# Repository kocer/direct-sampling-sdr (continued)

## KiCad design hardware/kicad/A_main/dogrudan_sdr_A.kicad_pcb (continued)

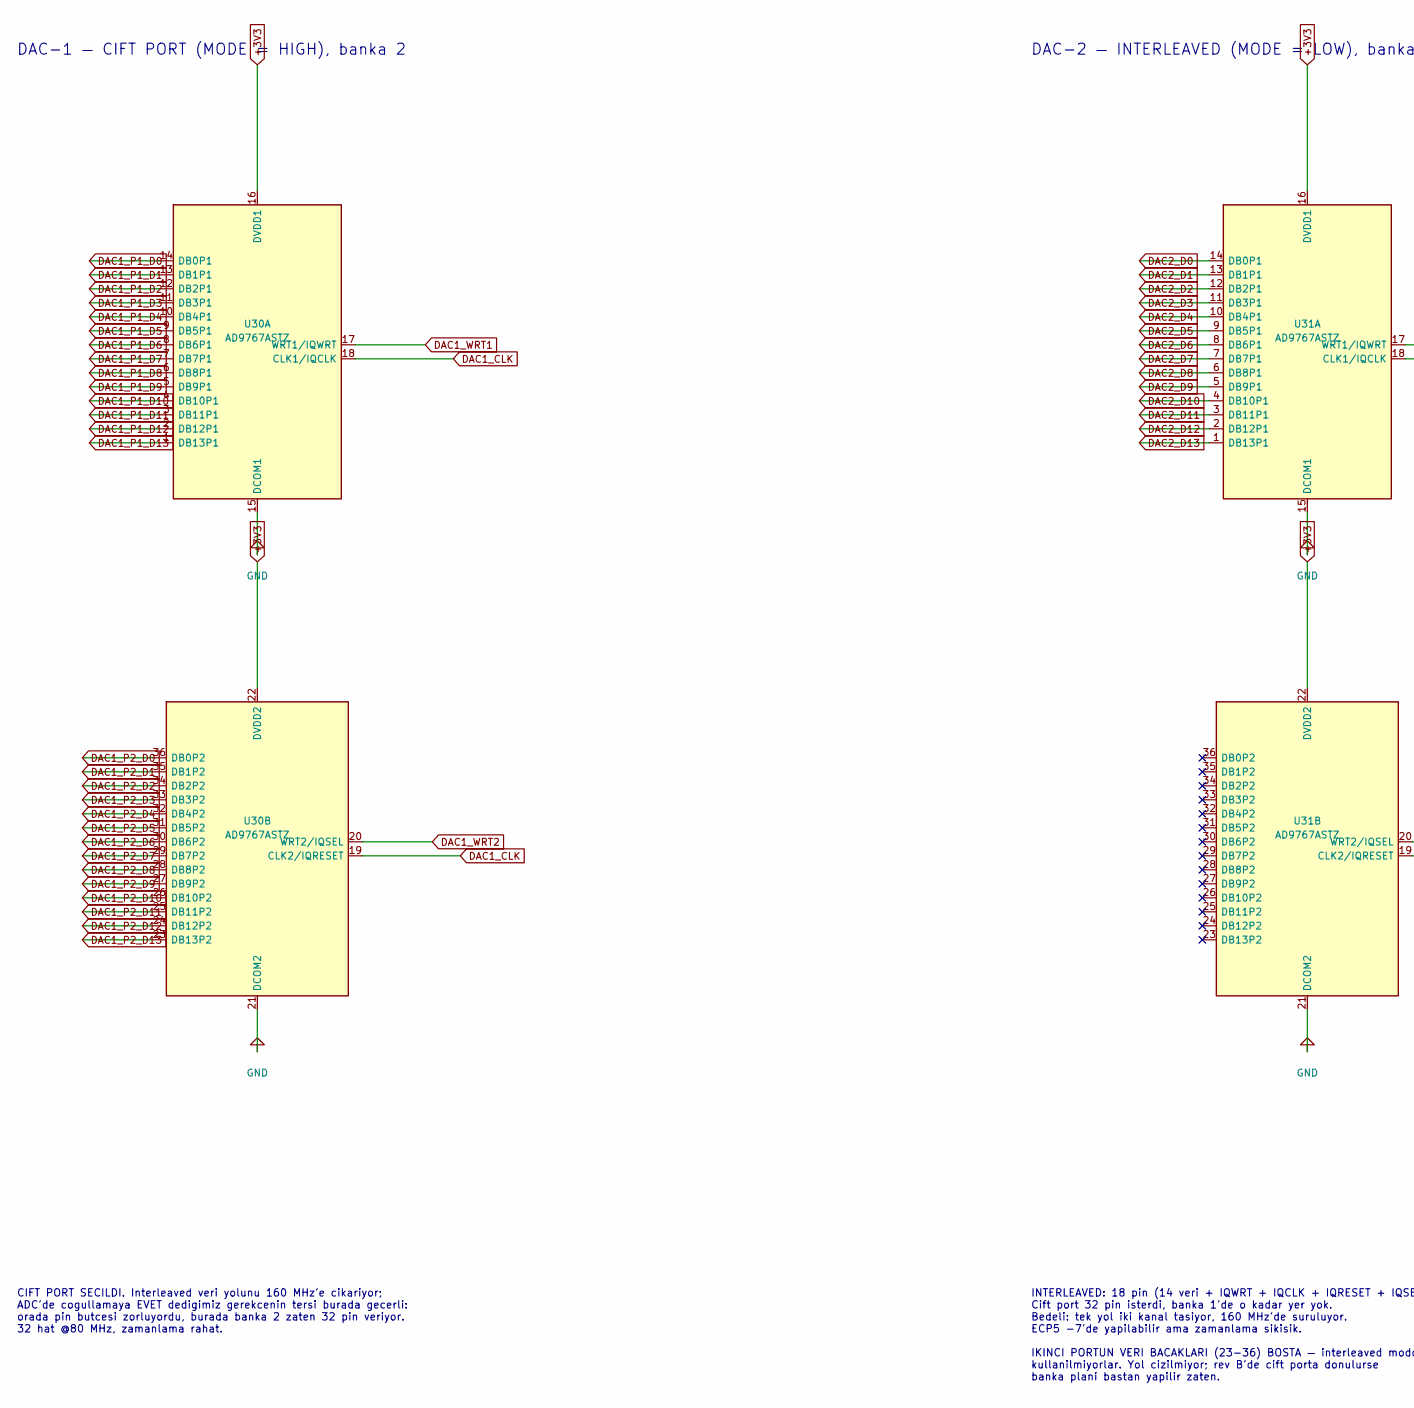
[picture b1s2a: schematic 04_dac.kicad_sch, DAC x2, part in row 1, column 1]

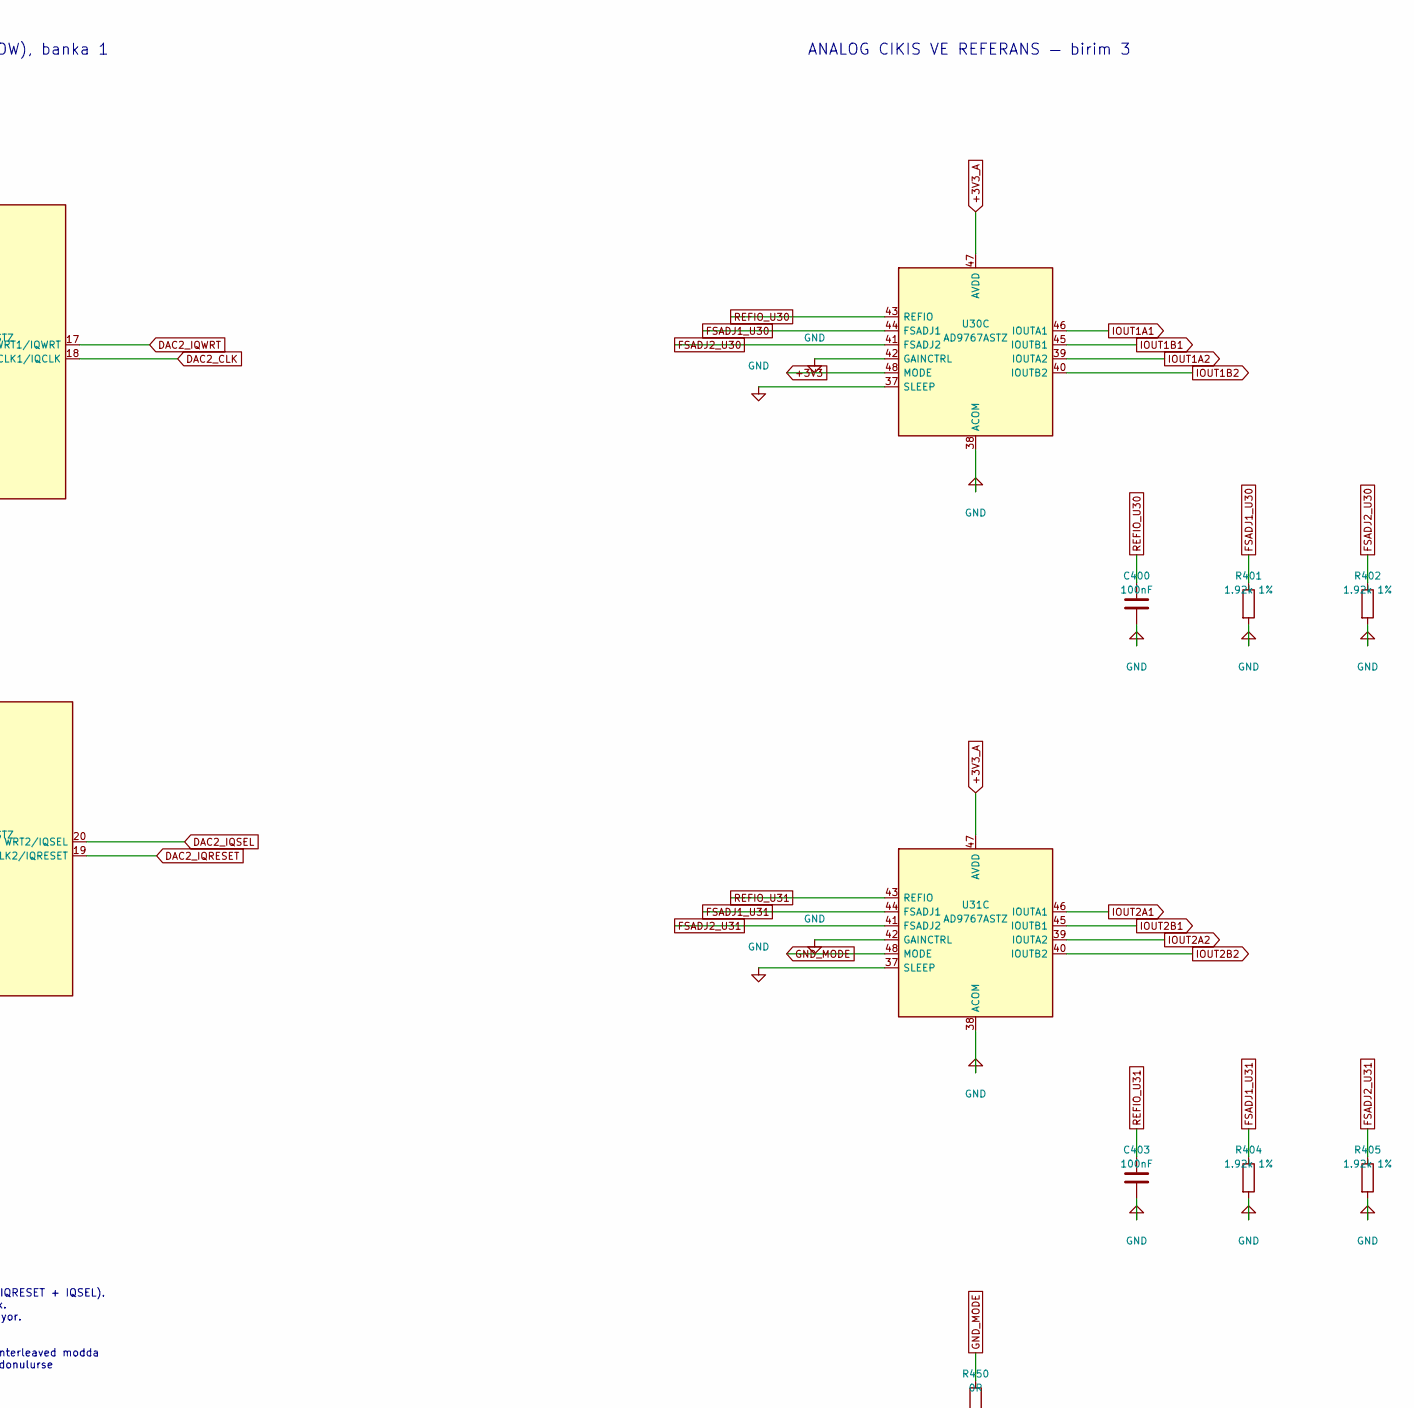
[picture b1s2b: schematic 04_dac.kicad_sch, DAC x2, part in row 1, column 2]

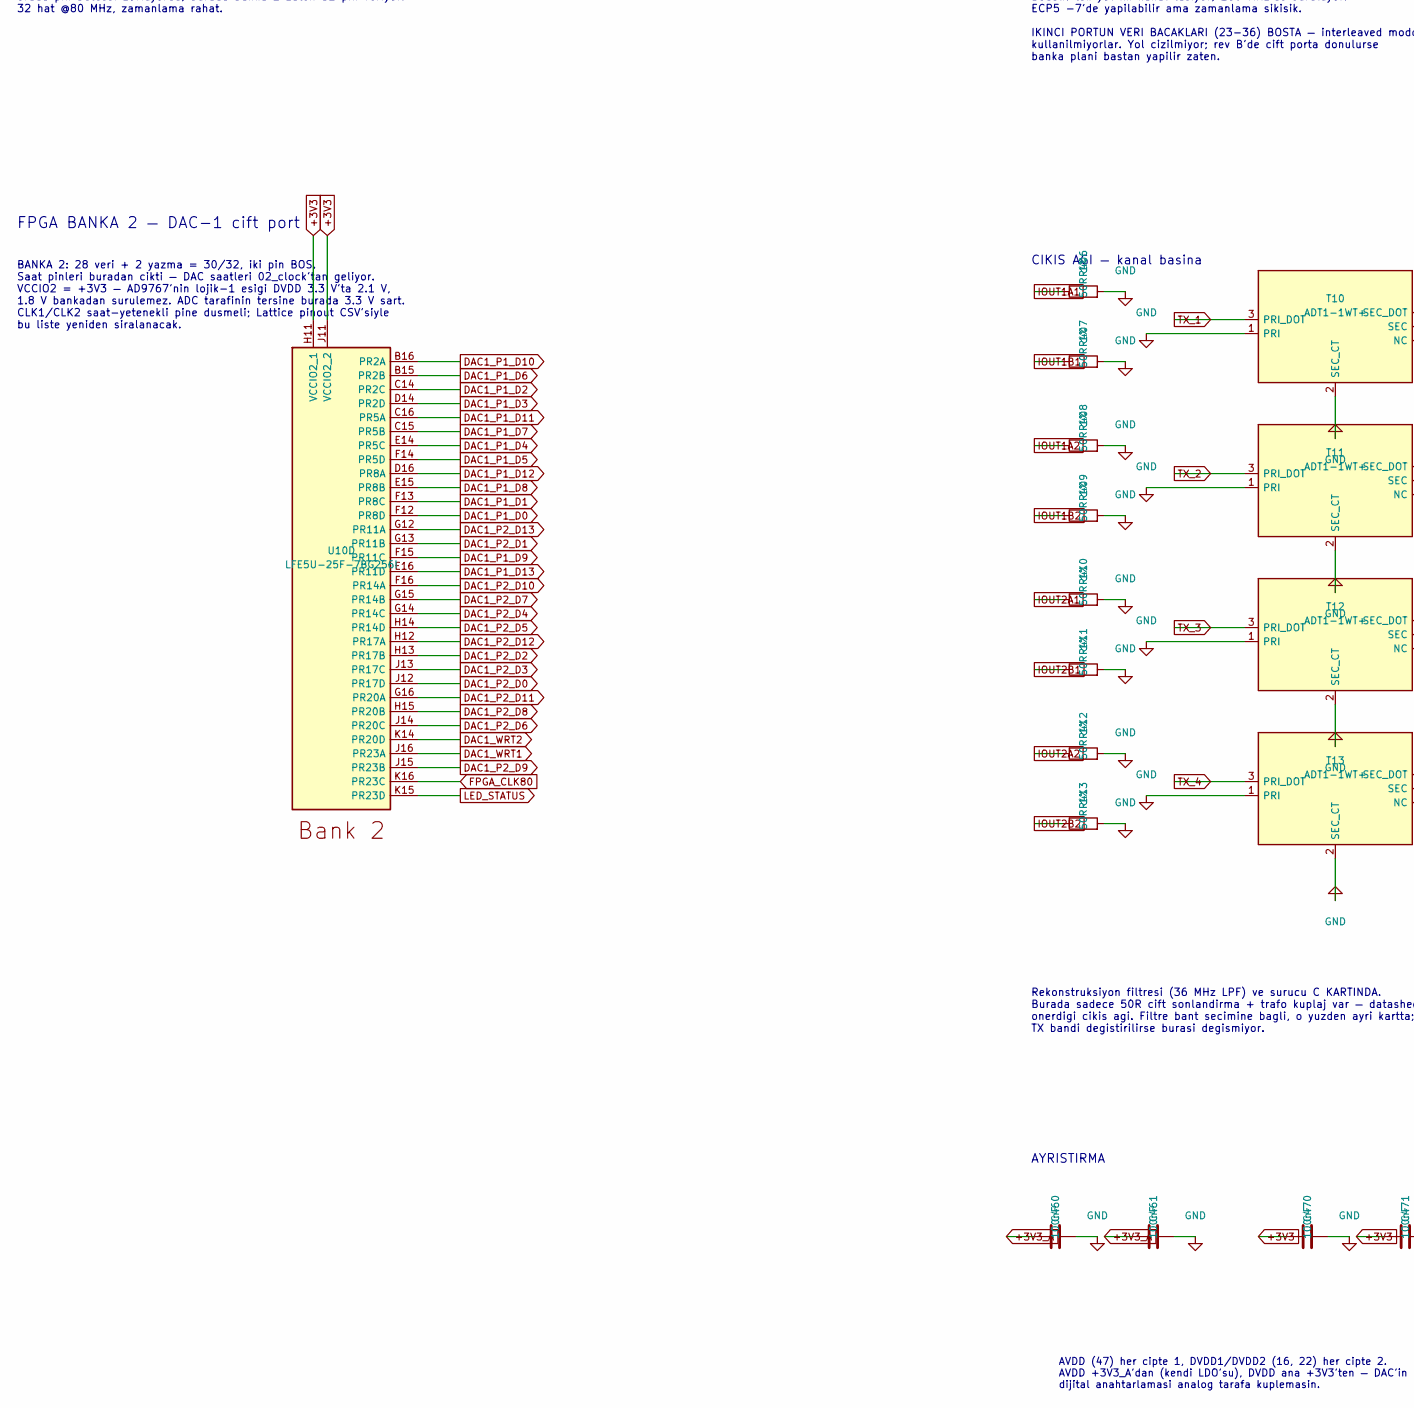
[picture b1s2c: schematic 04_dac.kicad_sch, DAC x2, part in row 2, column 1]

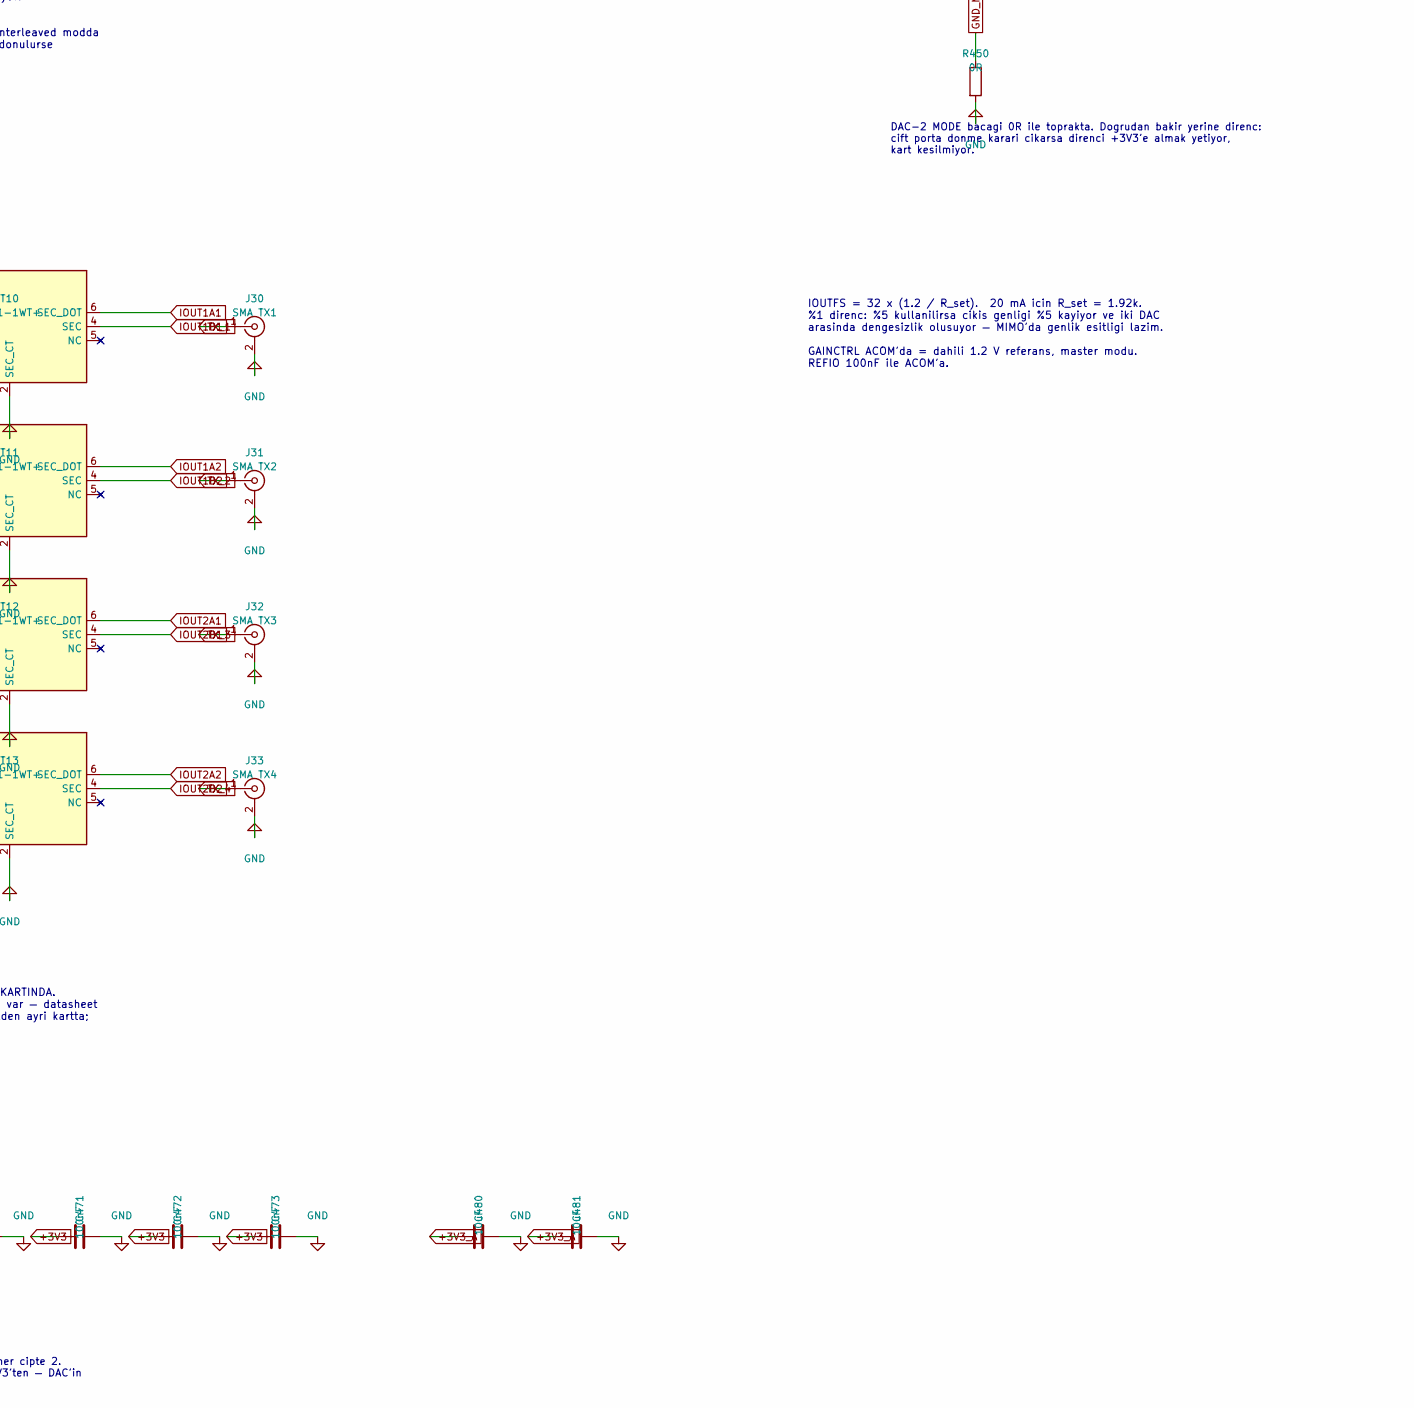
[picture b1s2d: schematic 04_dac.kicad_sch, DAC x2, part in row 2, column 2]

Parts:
C400, C403: 100nF; C_0603_1608Metric
C460, C461, C470, C471, C472, C473: 100nF; C_0402_1005Metric
C480, C481: 10uF; C_0402_1005Metric
J30: SMA TX1; SMA_Amphenol_132289_EdgeMount
J31: SMA TX2; SMA_Amphenol_132289_EdgeMount
J32: SMA TX3; SMA_Amphenol_132289_EdgeMount
J33: SMA TX4; SMA_Amphenol_132289_EdgeMount
R401, R402, R404, R405: 1.92k 1%; R_0603_1608Metric
R406, R407, R408, R409, R410, R411, R412, R413: 50R 1%; R_0603_1608Metric
R450: 0R; R_0603_1608Metric
T10, T11, T12, T13: ADT1-1WT+; Mini-Circuits_CD542_H2.84mm
U10: LFE5U-25F-7BG256I; BGA-256_14.0x14.0mm_Layout16x16_P0.8mm_Ball0.45mm_Pad0.32mm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
U30, U31: AD9767ASTZ; LQFP-48_7x7mm_P0.5mm

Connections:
DAC1_CLK: U30.18 (CLK1/IQCLK), U30.19 (CLK2/IQRESET); also elsewhere on the board
DAC1_P1_D0: U10.F12 (PR8D), U30.14 (DB0P1)
DAC1_P1_D1: U10.F13 (PR8C), U30.13 (DB1P1)
DAC1_P1_D2: U10.C14 (PR2C), U30.12 (DB2P1)
DAC1_P1_D3: U10.D14 (PR2D), U30.11 (DB3P1)
DAC1_P1_D4: U10.E14 (PR5C), U30.10 (DB4P1)
DAC1_P1_D5: U10.F14 (PR5D), U30.9 (DB5P1)
DAC1_P1_D6: U10.B15 (PR2B), U30.8 (DB6P1)
DAC1_P1_D7: U10.C15 (PR5B), U30.7 (DB7P1)
DAC1_P1_D8: U10.E15 (PR8B), U30.6 (DB8P1)
DAC1_P1_D9: U10.F15 (PR11C), U30.5 (DB9P1)
DAC1_P1_D10: U10.B16 (PR2A), U30.4 (DB10P1)
DAC1_P1_D11: U10.C16 (PR5A), U30.3 (DB11P1)
DAC1_P1_D12: U10.D16 (PR8A), U30.2 (DB12P1)
DAC1_P1_D13: U10.E16 (PR11D), U30.1 (DB13P1)
DAC1_P2_D0: U10.J12 (PR17D), U30.36 (DB0P2)
DAC1_P2_D1: U10.G13 (PR11B), U30.35 (DB1P2)
DAC1_P2_D2: U10.H13 (PR17B), U30.34 (DB2P2)
DAC1_P2_D3: U10.J13 (PR17C), U30.33 (DB3P2)
DAC1_P2_D4: U10.G14 (PR14C), U30.32 (DB4P2)
DAC1_P2_D5: U10.H14 (PR14D), U30.31 (DB5P2)
DAC1_P2_D6: U10.J14 (PR20C), U30.30 (DB6P2)
DAC1_P2_D7: U10.G15 (PR14B), U30.29 (DB7P2)
DAC1_P2_D8: U10.H15 (PR20B), U30.28 (DB8P2)
DAC1_P2_D9: U10.J15 (PR23B), U30.27 (DB9P2)
DAC1_P2_D10: U10.F16 (PR14A), U30.26 (DB10P2)
DAC1_P2_D11: U10.G16 (PR20A), U30.25 (DB11P2)
DAC1_P2_D12: U10.H12 (PR17A), U30.24 (DB12P2)
DAC1_P2_D13: U10.G12 (PR11A), U30.23 (DB13P2)
DAC1_WRT1: U10.J16 (PR23A), U30.17 (WRT1/IQWRT)
DAC1_WRT2: U10.K14 (PR20D), U30.20 (WRT2/IQSEL)
DAC2_CLK: U31.18 (CLK1/IQCLK); also elsewhere on the board
DAC2_D0: U31.14 (DB0P1); also elsewhere on the board
DAC2_D1: U31.13 (DB1P1); also elsewhere on the board
DAC2_D2: U31.12 (DB2P1); also elsewhere on the board
DAC2_D3: U31.11 (DB3P1); also elsewhere on the board
DAC2_D4: U31.10 (DB4P1); also elsewhere on the board
DAC2_D5: U31.9 (DB5P1); also elsewhere on the board
DAC2_D6: U31.8 (DB6P1); also elsewhere on the board
DAC2_D7: U31.7 (DB7P1); also elsewhere on the board
DAC2_D8: U31.6 (DB8P1); also elsewhere on the board
DAC2_D9: U31.5 (DB9P1); also elsewhere on the board
DAC2_D10: U31.4 (DB10P1); also elsewhere on the board
DAC2_D11: U31.3 (DB11P1); also elsewhere on the board
DAC2_D12: U31.2 (DB12P1); also elsewhere on the board
DAC2_D13: U31.1 (DB13P1); also elsewhere on the board
DAC2_IQRESET: U31.19 (CLK2/IQRESET); also elsewhere on the board
DAC2_IQSEL: U31.20 (WRT2/IQSEL); also elsewhere on the board
DAC2_IQWRT: U31.17 (WRT1/IQWRT); also elsewhere on the board
FPGA_CLK80: U10.K16 (PR23C); also elsewhere on the board
FSADJ1_U30: R401.1, U30.44 (FSADJ1)
FSADJ1_U31: R404.1, U31.44 (FSADJ1)
FSADJ2_U30: R402.1, U30.41 (FSADJ2)
FSADJ2_U31: R405.1, U31.41 (FSADJ2)
GND_MODE: R450.1, U31.48 (MODE)
IOUT1A1: R406.1, T10.6 (SEC_DOT), U30.46 (IOUTA1)
IOUT1A2: R408.1, T11.6 (SEC_DOT), U30.39 (IOUTA2)
IOUT1B1: R407.1, T10.4 (SEC), U30.45 (IOUTB1)
IOUT1B2: R409.1, T11.4 (SEC), U30.40 (IOUTB2)
IOUT2A1: R410.1, T12.6 (SEC_DOT), U31.46 (IOUTA1)
IOUT2A2: R412.1, T13.6 (SEC_DOT), U31.39 (IOUTA2)
IOUT2B1: R411.1, T12.4 (SEC), U31.45 (IOUTB1)
IOUT2B2: R413.1, T13.4 (SEC), U31.40 (IOUTB2)
LED_STATUS: U10.K15 (PR23D); also elsewhere on the board
TX_1: J30.1 (In), T10.3 (PRI_DOT)
TX_2: J31.1 (In), T11.3 (PRI_DOT)
TX_3: J32.1 (In), T12.3 (PRI_DOT)
TX_4: J33.1 (In), T13.3 (PRI_DOT)

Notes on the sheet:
INTERLEAVED: 18 pin (14 veri + IQWRT + IQCLK + IQRESET + IQSEL). Cift port 32 pin isterdi, banka 1'de o kadar yer yok. Bedeli: tek yol iki kanal tasiyor, 160 MHz'de suruluyor. ECP5 -7'de yapilabilir ama zamanlama sikisik. IKINCI PORTUN VERI BACAKLARI (23-36) BOSTA — interleaved modda kullanilmiyorl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
AYRISTIRMA
IOUTFS = 32 x (1.2 / R_set). 20 mA icin R_set = 1.92k. %1 direnc: %5 kullanilirsa cikis genligi %5 kayiyor ve iki DAC arasinda dengesizlik olusuyor — MIMO'da genlik esitligi lazim. GAINCTRL ACOM'da = dahili 1.2 V referans, master modu. REFIO 100nF ile ACOM'a.
BANKA 2: 28 veri + 2 yazma = 30/32, iki pin BOS. Saat pinleri buradan cikti — DAC saatleri 02_clock'tan geliyor. VCCIO2 = +3V3 — AD9767'nin lojik-1 esigi DVDD 3.3 V'ta 2.1 V, 1.8 V bankadan surulemez. ADC tarafinin tersine burada 3.3 V sart. CLK1/CLK2 saat-yetenekli pine dusmeli; Lattice pinout CSV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
ANALOG CIKIS VE REFERANS — birim 3
DAC-2 MODE bacagi 0R ile toprakta. Dogrudan bakir yerine direnc: cift porta donme karari cikarsa direnci +3V3'e almak yetiyor, kart kesilmiyor.
FPGA BANKA 2 — DAC-1 cift port
DAC-2 — INTERLEAVED (MODE = LOW), banka 1
CIKIS AGI — kanal basina
DAC-1 — CIFT PORT (MODE = HIGH), banka 2
CIFT PORT SECILDI. Interleaved veri yolunu 160 MHz'e cikariyor; ADC'de cogullamaya EVET dedigimiz gerekcenin tersi burada gecerli: orada pin butcesi zorluyordu, burada banka 2 zaten 32 pin veriyor. 32 hat @80 MHz, zamanlama rahat.
Rekonstruksiyon filtresi (36 MHz LPF) ve surucu C KARTINDA. Burada sadece 50R cift sonlandirma + trafo kuplaj var — datasheet onerdigi cikis agi. Filtre bant secimine bagli, o yuzden ayri kartta; TX bandi degistirilirse burasi degismiyor.
AVDD (47) her cipte 1, DVDD1/DVDD2 (16, 22) her cipte 2. AVDD +3V3_A'dan (kendi LDO'su), DVDD ana +3V3'ten — DAC'in dijital anahtarlamasi analog tarafa kuplemasin.
